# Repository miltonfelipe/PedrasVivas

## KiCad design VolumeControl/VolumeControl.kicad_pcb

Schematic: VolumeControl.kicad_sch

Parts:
C1: 100nF; C_0805_2012Metric_Pad1.18x1.45mm_HandSolder
C2, C3, C29: 100uF; CP_Elec_5x3.9
C4, C7, C8, C9, C10, C11, C14, C15, C16, C17, C20, C21: 10u; C_1210_3225Metric_Pad1.33x2.70mm_HandSolder
C5, C6, C12, C13, C18, C19, C22, C23: 50p; C_0805_2012Metric_Pad1.18x1.45mm_HandSolder
C24, C25, C26, C27, C28: 100nF; C_0805_2012Metric
D1, D3, D4, D5, D6, D7, D8: LED; LED_1210_3225Metric
D2: SS18; D_SMA
FB1: FerriteBead_Small; R_1206_3216Metric_Pad1.30x1.75mm_HandSolder
J1: Barrel_Jack; BarrelJack_CUI_PJ-063AH_Horizontal
J2, J3, J4, J8, J9, J12, J13: Conn_01x03; PinHeader_1x03_P1.00mm_Vertical
J5: XLR3_Ground
R1, R2, R3, R7, R8, R11, R12, R13, R14, R15: 100k; R_0805_2012Metric
R4, R5, R6, R9, R10, R18: 100R; R_0805_2012Metric
R16: 560R; R_0805_2012Metric
R17: 10R; R_0805_2012Metric
R19, R20, R21: 10K; R_0805_2012Metric
SW1: Select; SW_SPST_PTS647_Sx50
SW2: Up; SW_SPST_PTS647_Sx50
SW3: Down; SW_SPST_PTS647_Sx50
U1, U5, U7, U8: OPA1612AxD; SOIC-8_3.9x4.9mm_P1.27mm
U2, U4, U6: MCP4251-xxxx-SL; SOIC-14_3.9x8.7mm_P1.27mm
U3: L7812; TO-252-3_TabPin2
U10: LM1117MP-5.0; SOT-223-3_TabPin2
U12: ESP32-S3-DevKitC

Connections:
CS0: U2.1 (~CS), U12.16 (GPIO10/ADC1_CH9)
CS1: U4.1 (~CS)
CS2: U6.1 (~CS)
Down: R21.2, SW3.1
Earth: FB1.1, J2.3, J3.3, J4.3, J8.3, J9.3, J12.3, J13.3, R17.1
GND: C1.2, C2.2, C3.2, C5.1, C6.1, C12.1, C13.1, C18.1, C19.1, C22.1, C23.1, C24.2, C25.2, C26.2, C27.2, C28.2, C29.2, FB1.2, J1.2, J2.1, J3.1, J4.1, J8.1, J9.1, J12.1, J13.1, R1.2, R2.2, R3.2, R4.2, R5.2, R6.2, R7.2, R8.2, R9.2, R10.2, R11.2, R12.2, R13.2, R15.2, R16.2, R17.2, R18.2, SW1.2, SW2.2, SW3.2, U1.4 (V-), U2.4 (VSS), U3.2 (GND), U4.4 (VSS), U5.4 (V-), U6.4 (VSS), U7.4 (V-), U8.4 (V-), U10.1 (GND), U12.22 (GND), U12.23 (GND), U12.24 (GND), U12.44 (GND)
LED1: D3.2 (A)
LED2: D4.2 (A)
LED3: D5.2 (A)
LED4: D6.2 (A)
LED5: D7.2 (A)
LED6: D8.2 (A)
MISO: U2.13 (SDO), U4.13 (SDO), U6.13 (SDO), U12.19 (GPIO13/ADC2_CH2)
MOSI: U2.3 (SDI), U4.3 (SDI), U6.3 (SDI), U12.17 (GPIO11/ADC2_CH0)
unnamed: D1.1 (K), R16.1
unnamed: D2.2 (A), J1.1
unnamed: C3.1, D2.1 (K), U3.1 (IN)
unnamed: D3.1 (K), R4.1
unnamed: D4.1 (K), R5.1
unnamed: D5.1 (K), R6.1
unnamed: D6.1 (K), R9.1
unnamed: D7.1 (K), R10.1
unnamed: D8.1 (K), R18.1
unnamed: C8.1, C9.1, C10.1, C11.1, C16.1, C17.1, J2.2, R3.1
unnamed: C4.2, J3.2, R1.1
unnamed: C7.2, J4.2, R2.1
unnamed: C14.2, J8.2, R7.1
unnamed: C15.2, J9.2, R8.1
unnamed: C20.2, J12.2, R11.1
unnamed: C21.2, J13.2, R12.1
unnamed: R15.1, U8.7
unnamed: U1.3 (+), U2.9 (P0W)
unnamed: C4.1, C5.2, U1.1, U1.2 (-)
unnamed: U1.5 (+), U2.6 (P1W)
unnamed: C6.2, C7.1, U1.6 (-), U1.7
unnamed: C9.2, U2.8 (P0A)
unnamed: C8.2, U2.7 (P1A)
unnamed: C11.2, U4.8 (P0A)
unnamed: U4.9 (P0W), U5.3 (+)
unnamed: C10.2, U4.7 (P1A)
unnamed: U4.6 (P1W), U5.5 (+)
unnamed: C12.2, C14.1, U5.1, U5.2 (-)
unnamed: C13.2, C15.1, U5.6 (-), U5.7
unnamed: C17.2, U6.8 (P0A)
unnamed: U6.9 (P0W), U7.3 (+)
unnamed: C16.2, U6.7 (P1A)
unnamed: U6.6 (P1W), U7.5 (+)
unnamed: C18.2, C20.1, U7.1, U7.2 (-)
unnamed: C19.2, C21.1, U7.6 (-), U7.7
unnamed: C22.2, R13.1, R14.2, U8.3 (+)
REF: C23.2, U2.5 (P1B), U2.10 (P0B), U4.5 (P1B), U4.10 (P0B), U6.5 (P1B), U6.10 (P0B), U8.1, U8.2 (-)
SCK: U2.2 (SCK), U4.2 (SCK), U6.2 (SCK), U12.18 (GPIO12/ADC2_CH1)
Select: R19.2, SW1.1
UP: R20.2, SW2.1
V3V: R19.1, R20.1, R21.1, U12.1 (3V3), U12.2 (3V3)
V5V: C28.1, C29.1, U2.14 (VDD), U4.14 (VDD), U6.14 (VDD), U10.2 (VO), U12.21 (5V)
VCC: C1.1, C2.1, C24.1, C25.1, C26.1, C27.1, D1.2 (A), R14.1, U1.8 (V+), U3.3 (OUT), U5.8 (V+), U7.8 (V+), U8.8 (V+), U10.3 (VI)

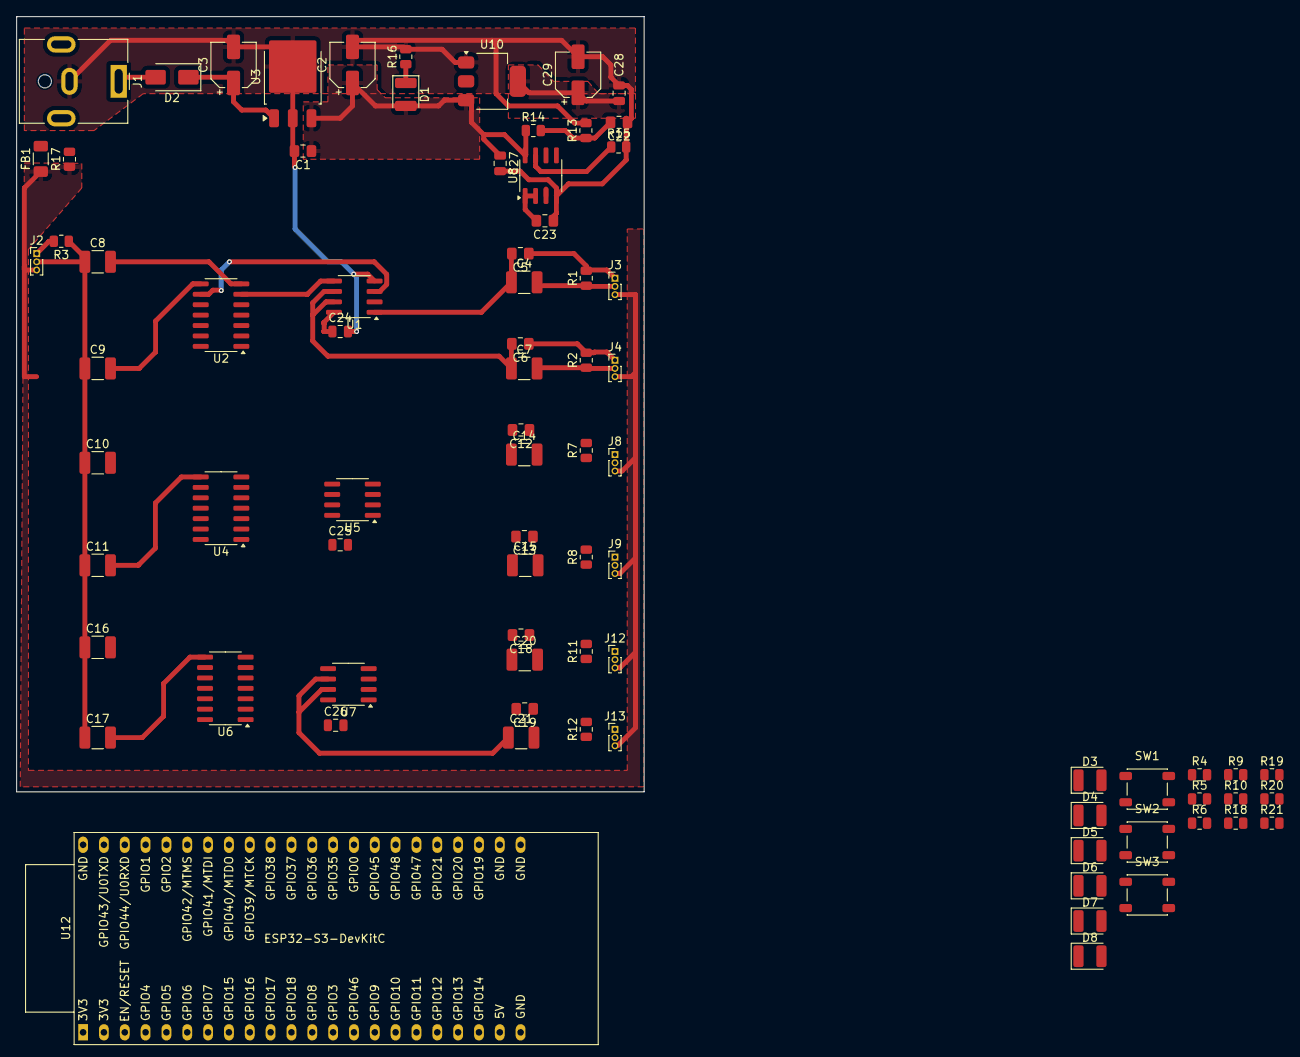
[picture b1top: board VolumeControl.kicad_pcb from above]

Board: 2 copper layers, 76.5 x 94.5 mm, 80 parts (0 on the bottom side), 49 nets.

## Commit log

2025-06-15 adv1
2025-06-15 6 Opamps
2025-06-15 circuito quase completo
2025-06-16 changing power supply of dig potentiometers
2025-06-16 Adding symbol of NodeMCU
2025-06-16 adding backups
2025-06-16 layout upates
2025-06-16 improvements on PCB design - PCB placement finished -missing controller
2025-06-22 simulation update, schematic update for only one input
2025-06-24 PPT first draft
